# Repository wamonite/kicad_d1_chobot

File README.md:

# d1_chobot

Central heating and hot water robot

Code: https://github.com/wamonite/arduino_d1_chobot

Used through hole MOSFETs and comparator as I have a lot of them to get through.

## Contact

          @wamonite     - twitter
           \_______.com - web
    warren____________/ - email

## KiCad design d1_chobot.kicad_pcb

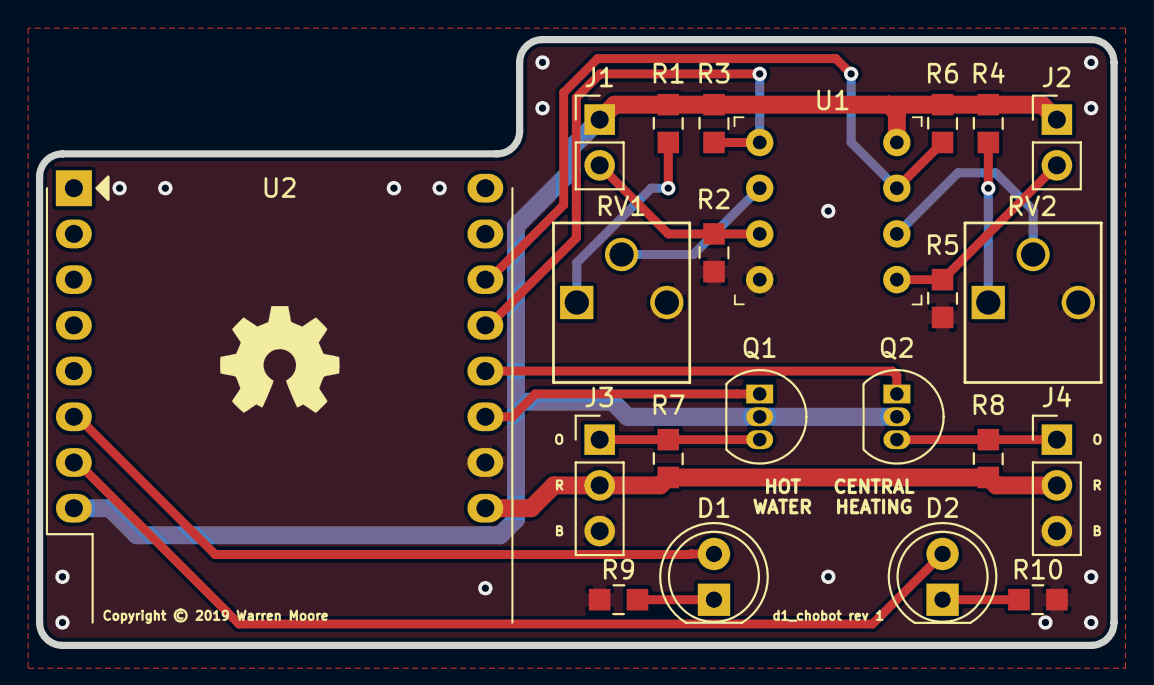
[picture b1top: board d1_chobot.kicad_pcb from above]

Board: 2 copper layers, 59.7 x 33.7 mm, 22 parts (0 on the bottom side), 19 nets.

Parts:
D1, D2: LED; LED_D5.0mm
J1: LDR HW; PinHeader_1x02_P2.54mm_Vertical
J2: LDR CH; PinHeader_1x02_P2.54mm_Vertical
J3: PWM HW; PinHeader_1x03_P2.54mm_Vertical
J4: PWM CH; PinHeader_1x03_P2.54mm_Vertical
Q1, Q2: 2N7000; TO-92_Inline
R1, R2, R3, R4, R5, R6: 10K; 0805
R7, R8, R9, R10: 2K2; 0805
RV1, RV2: 100K; 3306P-1-202
U1: LM393; SOCKET_DIP-8_7.62mm_Conn
U2: WeMos_D1_mini; WEMOS_D1_mini_light

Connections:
+3V3: J1.1, J2.1, Q1.2, Q2.2, R1.1, R3.1, R4.1, R6.1, U1.8, U2.8
+5V: J3.2, J4.2, R7.1, R8.1, U2.9
GND: J3.3, J4.3, R2.2, R5.2, R9.2, R10.2, RV1.3, RV2.3, U1.4, U2.10
LDR_CH: R6.2, U1.7, U2.14
LDR_HW: R3.2, U1.1, U2.13
LED_CH: D2.2, U2.7
LED_HW: D1.2, U2.6
unnamed: D1.1, R9.1
unnamed: D2.1, R10.1
unnamed: J1.2, R2.1, U1.3
unnamed: J2.2, R5.1, U1.5
unnamed: J3.1, Q1.3, R7.2
unnamed: J4.1, Q2.3, R8.2
unnamed: R1.2, RV1.1
unnamed: R4.2, RV2.1
unnamed: RV1.2, U1.2
unnamed: RV2.2, U1.6
PWM_CH: Q2.1, U2.12
PWM_HW: Q1.1, U2.11

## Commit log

2019-09-07 Added ignore.
2019-09-07 Updated ignore.
2019-09-07 Initial commit.
2019-09-07 Add schematic PDF and README.
2019-09-07 Add ORB to PWM jumpers.
2019-09-07 Update README.
2019-09-07 Added vias.
2019-09-15 Add README notes.

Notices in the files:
d1_chobot.kicad_pcb:
Copyright © 2019 Warren Moore
parts and their libraries:
Copyright 2016 Accelerated Designs. All rights reserved.
